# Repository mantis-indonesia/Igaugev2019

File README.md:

# Igaugev2019
Open source hardware water pressure sensor measurement system using Arduino Mega 2560

# Development
This system develop by Team MANTIS ID collaborate with USAID - IUWASH PLUS, PDAM Tirta Pakuan Kota Bogor, PDAM Tirta Patriot Kota Bekasi, and PDAM Tirta Asasta Kota Depok

# Folder
1. **Arduino Library** : All arduino external library used in this development
2. **Igauge_V2019** : Arduino Sketch used in this system
3. **Manual & Material** : All datasheet, and learning materials from components used in this system
4. **WEMOS_IGAUGE** : Arduino sketch for ESP Unit System
5. **nRFRangeTestRX** : Arduino sketch for NRF24L01 Experiment. This sketch used in server side
6. **nRFRangeTestTX** : Arduino sketch for NRF24L01 Experiment. This sketch used in transmitter side

# Developer
- Hollanda Arief Kusuma : github.com/hollandacocobear
- Rady P

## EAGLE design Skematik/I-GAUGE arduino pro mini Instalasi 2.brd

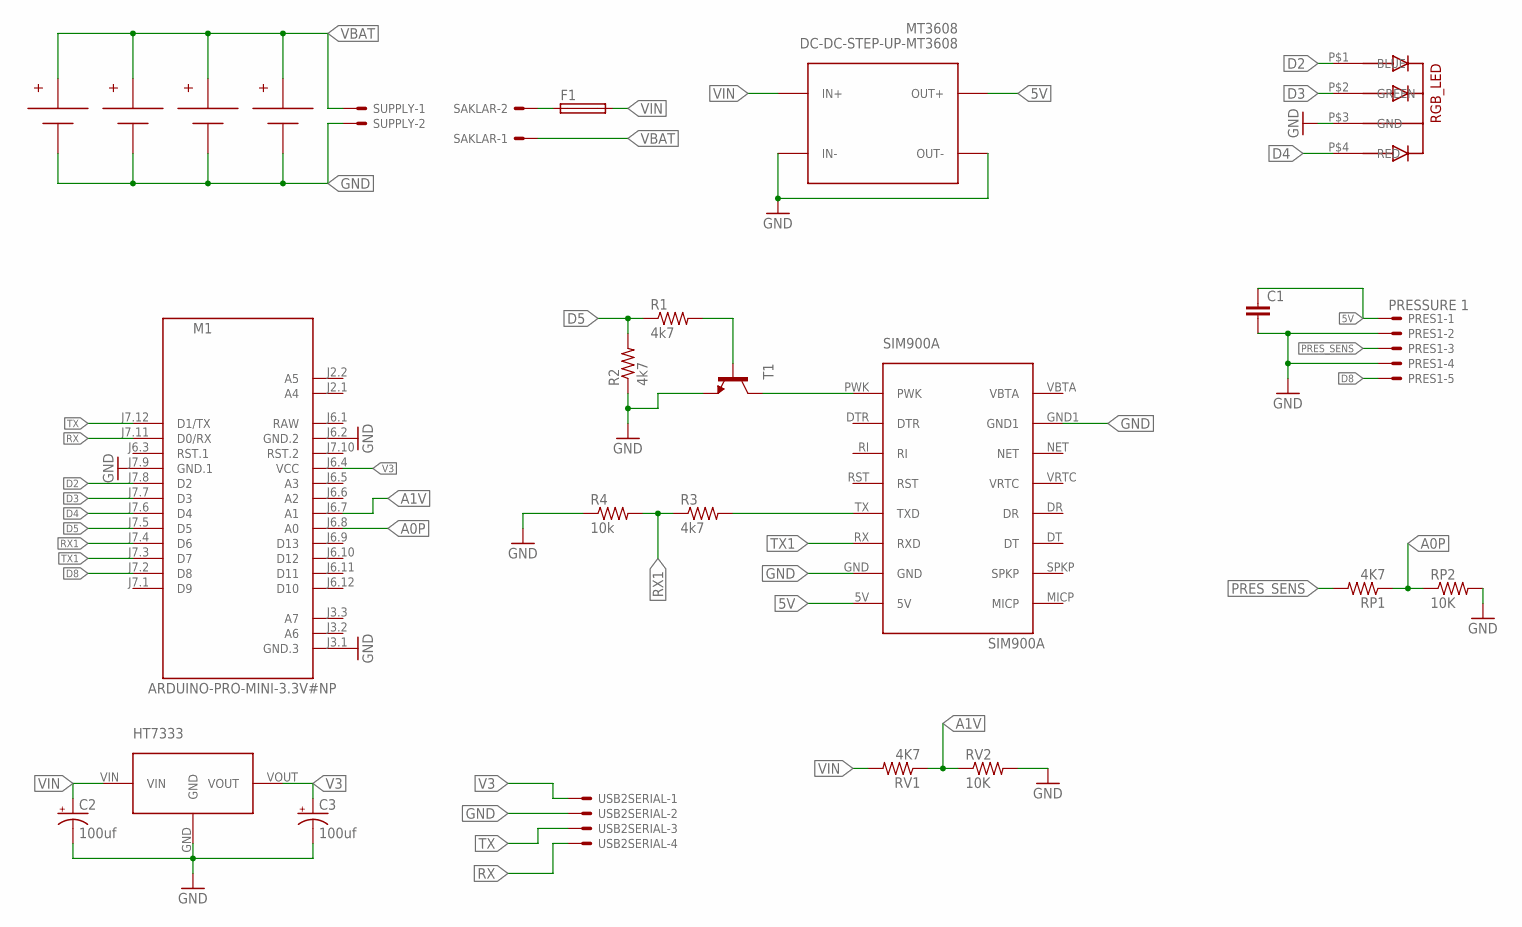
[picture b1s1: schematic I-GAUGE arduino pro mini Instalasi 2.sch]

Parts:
C1: C-EUC1206; C1206
C2, C3: 100uf; CT7343
F1: FUSESH22,5; SH22,5
HT7333: HT7333_SOT89; SOT89
M1: ARDUINO-PRO-MINI-3.3V#NP; ARDUINO-PRO-MINI#NP
MT3608: DC-DC-STEP-UP-MT3608
PRES1: PRESSURE 1; JST-XH-05-PACKAGE-ROUND-PAD
R1, R2: 4k7; R1206
R3: 4k7; 1206
R4: 10k; R1206
RGB_LED: 5MMRGBLED; LED5MMRGB
RP1: 4K7; M1206
RP2: 10K; M1206
RV1: 4K7; M1206
RV2: 10K; M1206
SAKLAR: JST-XH-02-PIN-ROUND-PAD; JST-XH-02-PACKAGE-ROUND-PAD
SUPPLY: JST-XH-02-PIN-ROUND-PAD; JST-XH-02-PACKAGE-ROUND-PAD
T1: -NPN-TO92; TO92
U$1, U$2, U$3, U$4: SMT18650; 18650SMT
U$6: SIM900A
USB2SERIAL: JST-XH-04-PIN-ROUND-PAD; JST-XH-04-PACKAGE-ROUND-PAD

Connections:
5V: C1.1, MT3608.OUT+, PRES1.1, U$6.5V
A0P: M1.J6.8 (A0), RP1.1, RP2.1
A1V: M1.J6.7 (A1), RV1.1, RV2.1
D2: M1.J7.8 (D2), RGB_LED.P$1 (BLUE)
D3: M1.J7.7 (D3), RGB_LED.P$2 (GREEN)
D4: M1.J7.6 (D4), RGB_LED.P$4 (RED)
D5: M1.J7.5 (D5), R1.1, R2.2
D8: M1.J7.2 (D8), PRES1.5
GND: C1.2, C2.-, C3.-, HT7333.GND, M1.J3.1 (GND.3), M1.J6.2 (GND.2), M1.J7.9 (GND.1), MT3608.IN-, MT3608.OUT-, PRES1.2, PRES1.4, R2.1, R4.1, RGB_LED.P$3 (GND), RP2.2, RV2.2, SUPPLY.2, T1.1 (E), U$1.BATTERY_NEGATIVE (-), U$2.BATTERY_NEGATIVE (-), U$3.BATTERY_NEGATIVE (-), U$4.BATTERY_NEGATIVE (-), U$6.GND, U$6.GND1, USB2SERIAL.2
unnamed: R1.2, T1.2 (B)
unnamed: R3.2, U$6.TX (TXD)
unnamed: T1.3 (C), U$6.PWK
PRES_SENS: PRES1.3, RP1.2
RAW: M1.J6.1 (RAW)
RX: M1.J7.11 (D0/RX), USB2SERIAL.4
RX1: M1.J7.4 (D6), R3.1, R4.2
TX: M1.J7.12 (D1/TX), USB2SERIAL.3
TX1: M1.J7.3 (D7), U$6.RX (RXD)
V3: C3.+, HT7333.VOUT, M1.J6.4 (VCC), USB2SERIAL.1
VBAT: SAKLAR.1, SUPPLY.1, U$1.BATTERY_POSITIVE (+), U$2.BATTERY_POSITIVE (+), U$3.BATTERY_POSITIVE (+), U$4.BATTERY_POSITIVE (+)
VCC: F1.1, SAKLAR.2
VIN: C2.+, F1.2, HT7333.VIN, MT3608.IN+, RV1.2

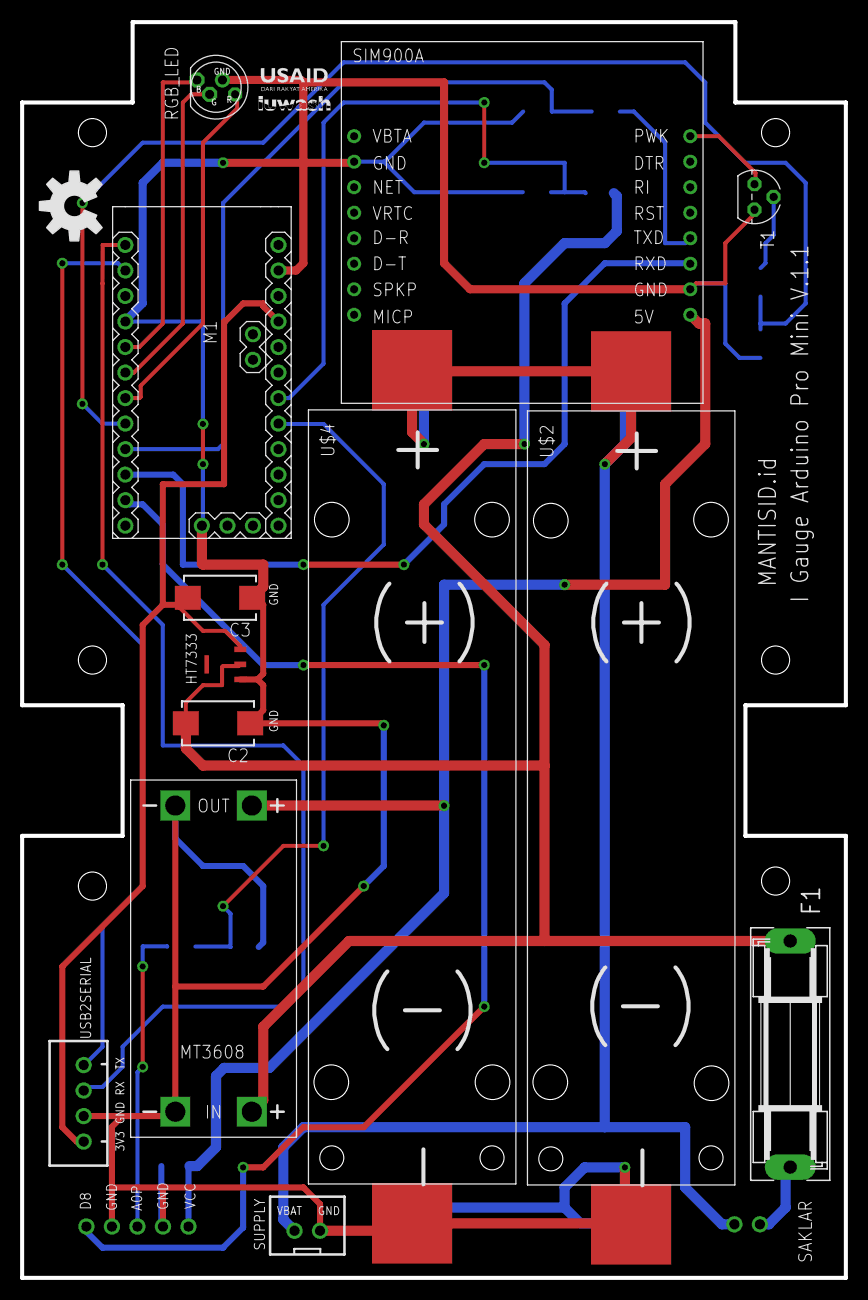
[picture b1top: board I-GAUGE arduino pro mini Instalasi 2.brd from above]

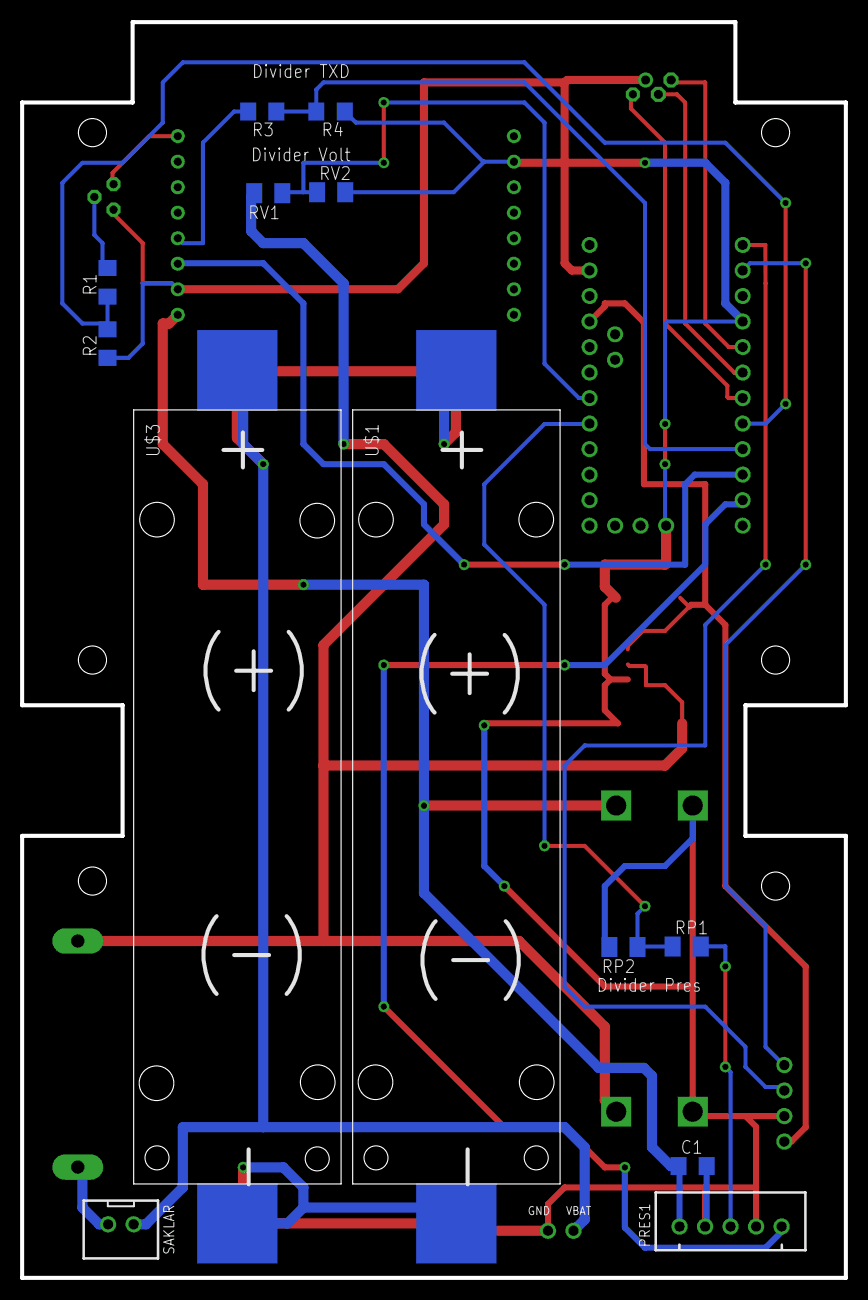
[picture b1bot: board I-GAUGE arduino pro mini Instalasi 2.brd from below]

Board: 2 copper layers, 82.0 x 125.0 mm, 27 parts (13 on the bottom side), 21 nets.

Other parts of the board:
U$7: OSHW-LOGO-L

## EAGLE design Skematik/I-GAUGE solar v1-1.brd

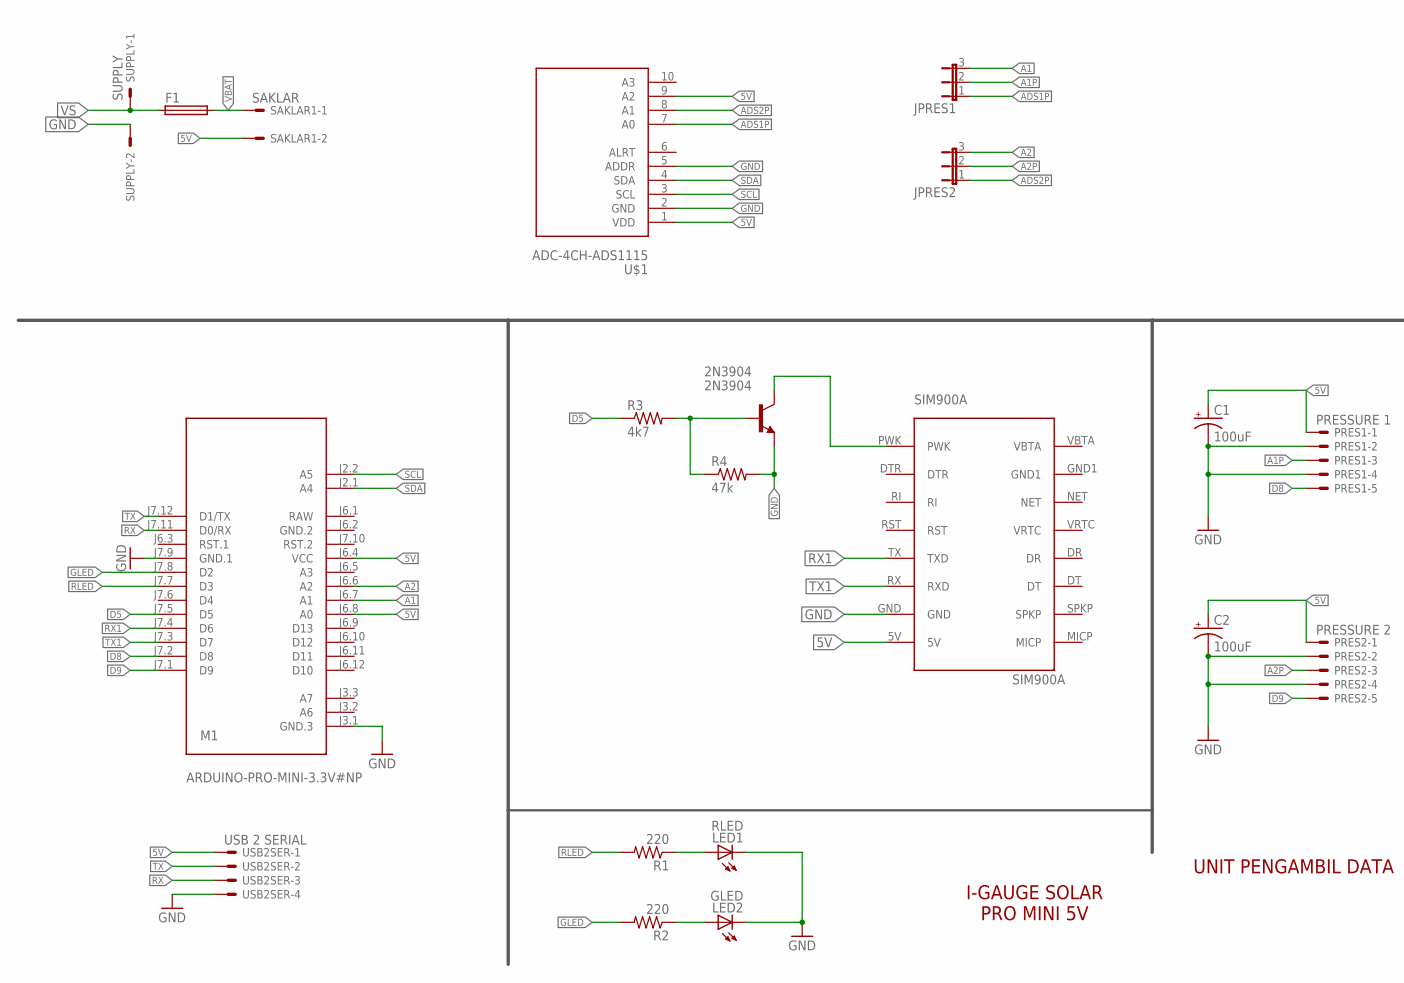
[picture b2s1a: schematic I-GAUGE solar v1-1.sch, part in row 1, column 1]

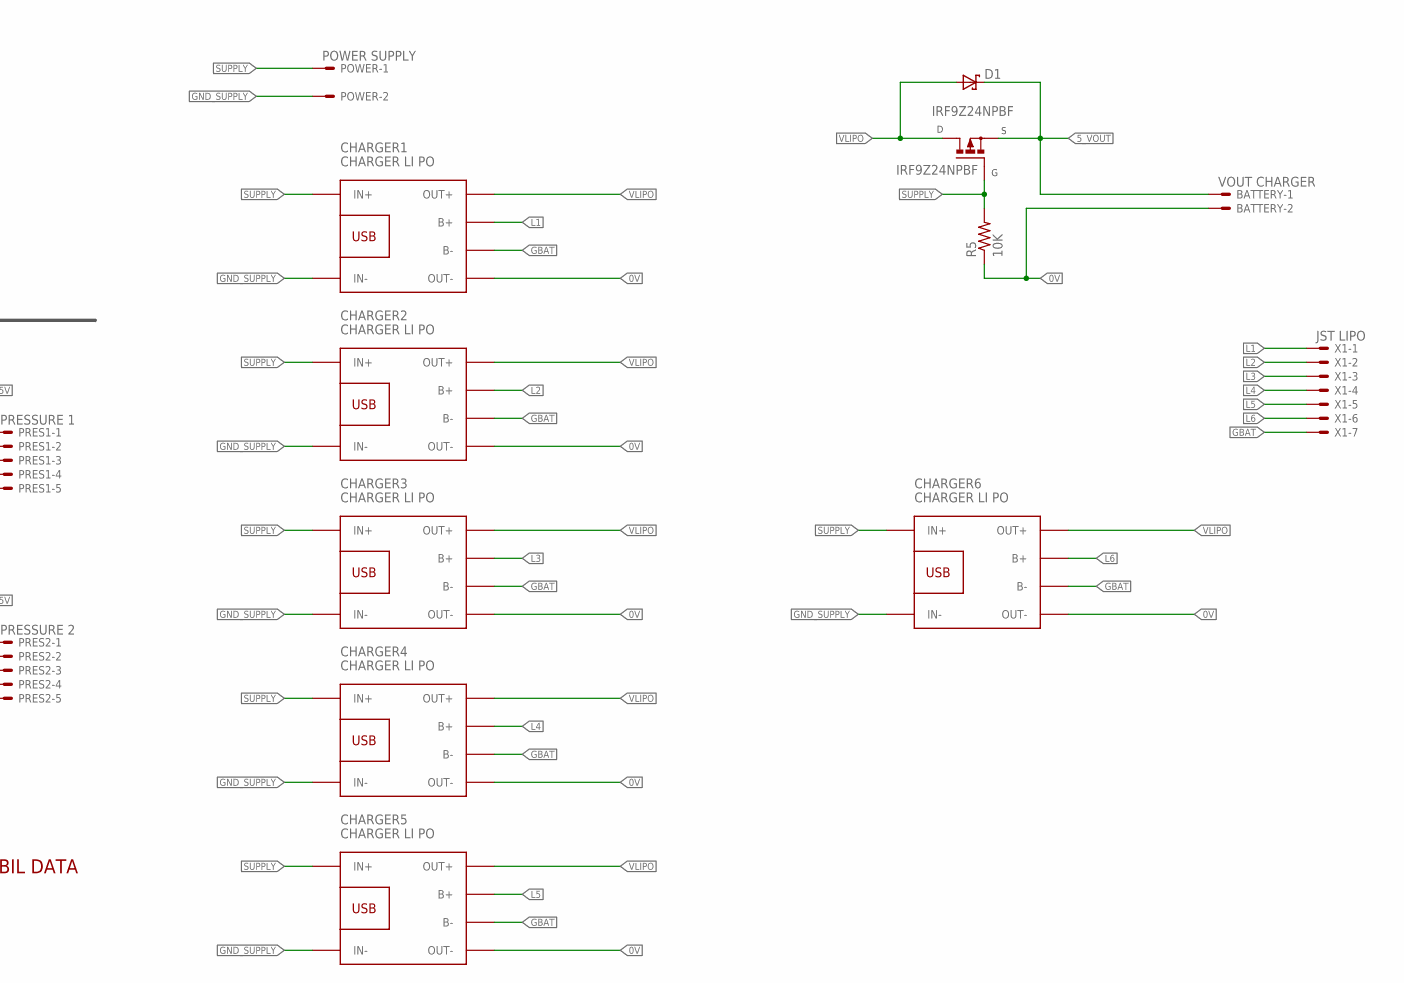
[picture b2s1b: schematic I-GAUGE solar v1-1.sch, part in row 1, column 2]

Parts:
2N3904: 2N3904; TO92
BATTERY: VOUT CHARGER; JST-XH-02-PACKAGE-ROUND-PAD
C1, C2: 100uF; EIA7343
CHARGER1, CHARGER2, CHARGER3, CHARGER4, CHARGER5, CHARGER6: CHARGER LI PO; BATTERY-CHARGER-LI-PROT
D1: DS_E2L; E2LINE
F1: FUSESH22,5; SH22,5
IRF9Z24NPBF: IRF9Z24NPBF; TO220BH
JPRES1, JPRES2: JP2E; JP2
LED1: RLED; LED5MM
LED2: GLED; LED5MM
M1: ARDUINO-PRO-MINI-3.3V#NP; ARDUINO-PRO-MINI#NP
POWER: POWER SUPPLY; JST-XH-02-PACKAGE-ROUND-PAD
PRES1: PRESSURE 1; JST-XH-05-PACKAGE-ROUND-PAD
PRES2: PRESSURE 2; JST-XH-05-PACKAGE-ROUND-PAD
R1, R2: 220; M1206
R3: 4k7; R0805
R4: 47k; R0805
R5: 10K; R0805
SAKLAR1: SAKLAR; JST-XH-02-PACKAGE-ROUND-PAD
SUPPLY: SUPPLY; JST-XH-02-PACKAGE-ROUND-PAD
U$1: ADC-4CH-ADS1115
U$5: SIM900A
USB2SER: USB 2 SERIAL; JST-XH-04-PACKAGE-ROUND-PAD
X1: JST LIPO; JST-XH-07-PACKAGE-ROUND-PAD

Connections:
0V: BATTERY.2, CHARGER1.OUT-, CHARGER2.OUT-, CHARGER3.OUT-, CHARGER4.OUT-, CHARGER5.OUT-, CHARGER6.OUT-, R5.1
5V: C1.A (+), C2.A (+), M1.J6.4 (VCC), M1.J6.8 (A0), PRES1.1, PRES2.1, SAKLAR1.2, U$1.1 (VDD), U$1.9 (A2), U$5.5V, USB2SER.1
5_VOUT: BATTERY.1, D1.1 (K), IRF9Z24NPBF.S
A1: JPRES1.3, M1.J6.7 (A1)
A1P: JPRES1.2, PRES1.3
A2: JPRES2.3, M1.J6.6 (A2)
A2P: JPRES2.2, PRES2.3
ADS1P: JPRES1.1, U$1.7 (A0)
ADS2P: JPRES2.1, U$1.8 (A1)
D5: M1.J7.5 (D5), R3.1
D8: M1.J7.2 (D8), PRES1.5
D9: M1.J7.1 (D9), PRES2.5
GBAT: CHARGER1.B-, CHARGER2.B-, CHARGER3.B-, CHARGER4.B-, CHARGER5.B-, CHARGER6.B-, X1.7
GLED: M1.J7.8 (D2), R2.2
GND: 2N3904.3 (E), C1.C (-), C2.C (-), LED1.K (C), LED2.K (C), M1.J3.1 (GND.3), M1.J7.9 (GND.1), PRES1.2, PRES1.4, PRES2.2, PRES2.4, R4.2, SUPPLY.2, U$1.2 (GND), U$1.5 (ADDR), U$5.GND, USB2SER.4
GND.2: M1.J6.2 (GND.2)
GND_SUPPLY: CHARGER1.IN-, CHARGER2.IN-, CHARGER3.IN-, CHARGER4.IN-, CHARGER5.IN-, CHARGER6.IN-, POWER.2
L1: CHARGER1.B+, X1.1
L2: CHARGER2.B+, X1.2
L3: CHARGER3.B+, X1.3
L4: CHARGER4.B+, X1.4
L5: CHARGER5.B+, X1.5
L6: CHARGER6.B+, X1.6
unnamed: 2N3904.1 (C), U$5.PWK
unnamed: LED1.A, R1.1
unnamed: LED2.A, R2.1
unnamed: 2N3904.2 (B), R3.2, R4.1
RAW: M1.J6.1 (RAW)
RLED: M1.J7.7 (D3), R1.2
RX: M1.J7.11 (D0/RX), USB2SER.3
RX1: M1.J7.4 (D6), U$5.TX (TXD)
SCL: M1.J2.2 (A5), U$1.3 (SCL)
SDA: M1.J2.1 (A4), U$1.4 (SDA)
SUPPLY: CHARGER1.IN+, CHARGER2.IN+, CHARGER3.IN+, CHARGER4.IN+, CHARGER5.IN+, CHARGER6.IN+, IRF9Z24NPBF.G, POWER.1, R5.2
TX: M1.J7.12 (D1/TX), USB2SER.2
TX1: M1.J7.3 (D7), U$5.RX (RXD)
VBAT: F1.2, SAKLAR1.1
VLIPO: CHARGER1.OUT+, CHARGER2.OUT+, CHARGER3.OUT+, CHARGER4.OUT+, CHARGER5.OUT+, CHARGER6.OUT+, D1.2 (A), IRF9Z24NPBF.D
VS: F1.1, SUPPLY.1

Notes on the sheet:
I-GAUGE SOLAR PRO MINI 5V
UNIT PENGAMBIL DATA

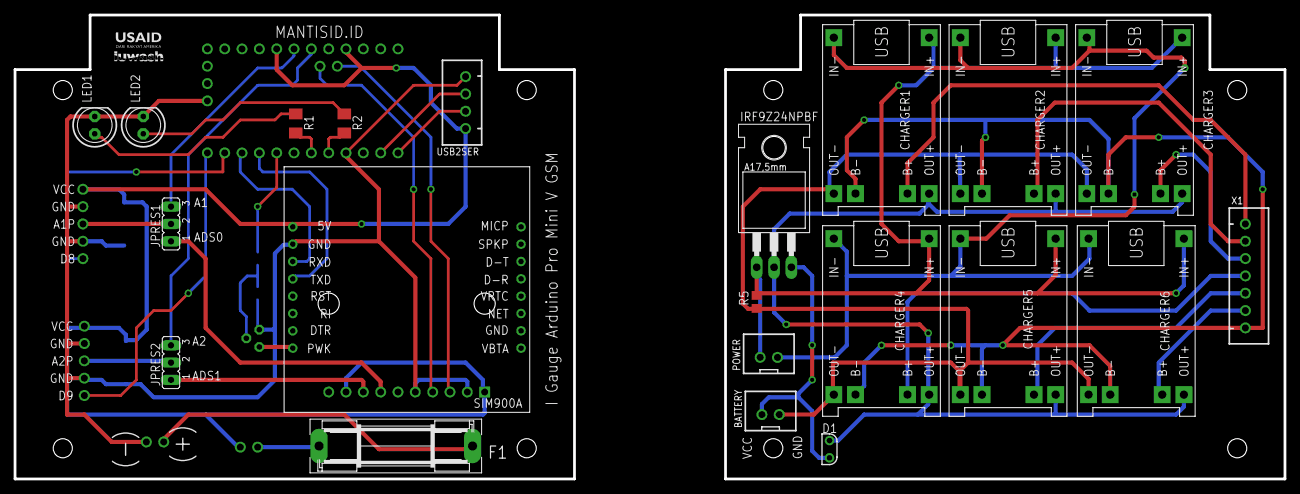
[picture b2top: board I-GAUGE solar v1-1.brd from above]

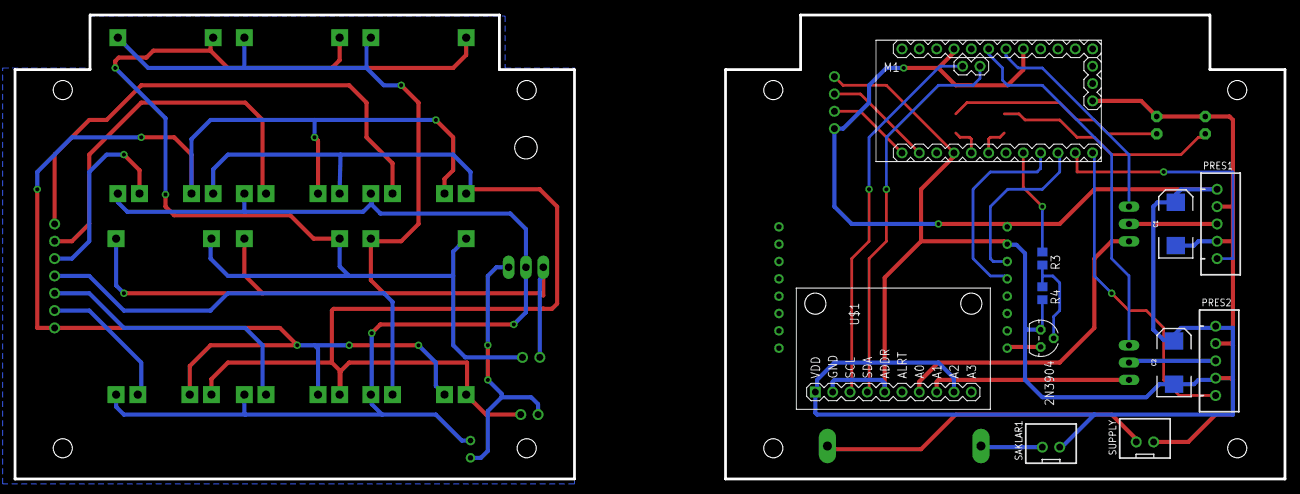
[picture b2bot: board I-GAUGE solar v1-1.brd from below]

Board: 2 copper layers, 186.1 x 68.0 mm, 32 parts (11 on the bottom side), 37 nets.

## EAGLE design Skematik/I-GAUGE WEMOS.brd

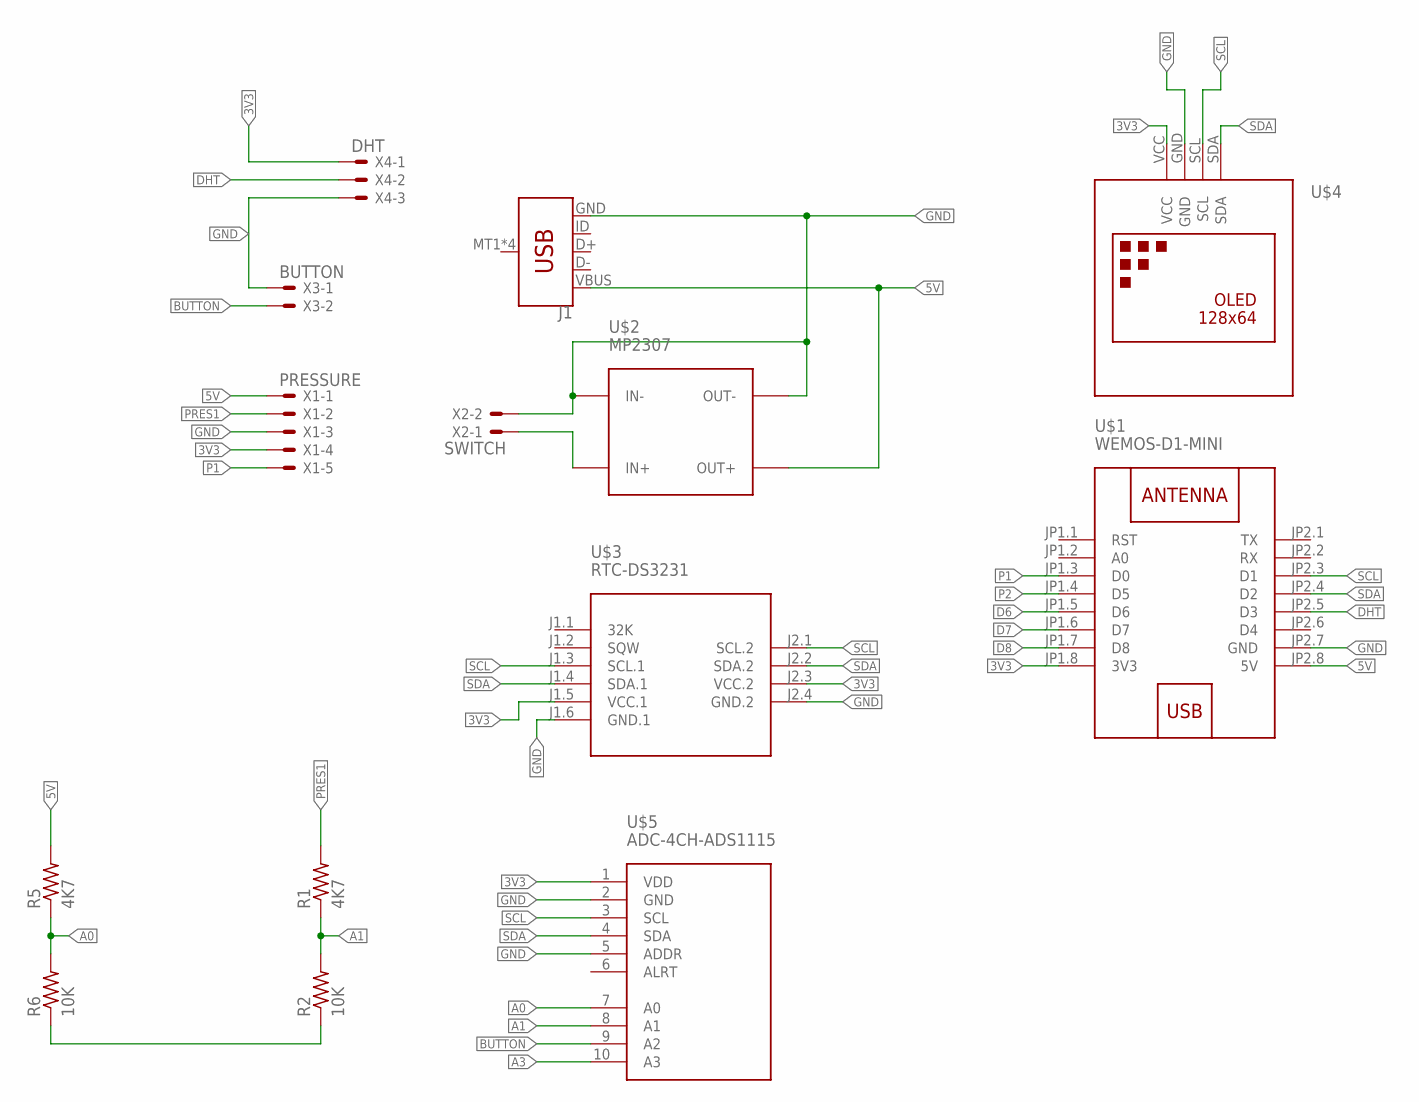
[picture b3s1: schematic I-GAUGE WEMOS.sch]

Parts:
J1: USB_MICRO-B_SMT; USB-MICROB
R1, R5: 4K7; R1210
R2, R6: 10K; R1210
U$1: WEMOS-D1-MINI
U$2: MP2307; DC-DC-STEP-DOWN-MP2307
U$3: RTC-DS3231; RTC-DS3231-AT24C32
U$4: DISPLAY-OLED-128X64-I2C
U$5: ADC-4CH-ADS1115
X1: PRESSURE; JST-XH-05-PACKAGE-LONG-PAD
X2: SWITCH; JST-XH-02-PACKAGE-LONG-PAD
X3: BUTTON; JST-XH-02-PACKAGE-LONG-PAD
X4: DHT; JST-XH-03-PACKAGE-LONG-PAD

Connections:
3V3: U$1.JP1.8 (3V3), U$3.J1.5 (VCC.1), U$3.J2.3 (VCC.2), U$4.VCC, U$5.1 (VDD), X1.4, X4.1
5V: J1.VBUS, R5.2, U$1.JP2.8 (5V), U$2.OUT+, X1.1
A0: R5.1, R6.2, U$5.7 (A0)
A1: R1.1, R2.2, U$5.8 (A1)
A3: U$5.10 (A3)
BUTTON: U$5.9 (A2), X3.2
D6: U$1.JP1.5 (D6)
D7: U$1.JP1.6 (D7)
D8: U$1.JP1.7 (D8)
DHT: U$1.JP2.5 (D3), X4.2
GND: J1.GND, R2.1, R6.1, U$1.JP2.7 (GND), U$2.IN-, U$2.OUT-, U$3.J1.6 (GND.1), U$3.J2.4 (GND.2), U$4.GND, U$5.2 (GND), U$5.5 (ADDR), X1.3, X2.2, X3.1, X4.3
unnamed: U$2.IN+, X2.1
P1: U$1.JP1.3 (D0), X1.5
P2: U$1.JP1.4 (D5)
PRES1: R1.2, X1.2
SCL: U$1.JP2.3 (D1), U$3.J1.3 (SCL.1), U$3.J2.1 (SCL.2), U$4.SCL, U$5.3 (SCL)
SDA: U$1.JP2.4 (D2), U$3.J1.4 (SDA.1), U$3.J2.2 (SDA.2), U$4.SDA, U$5.4 (SDA)

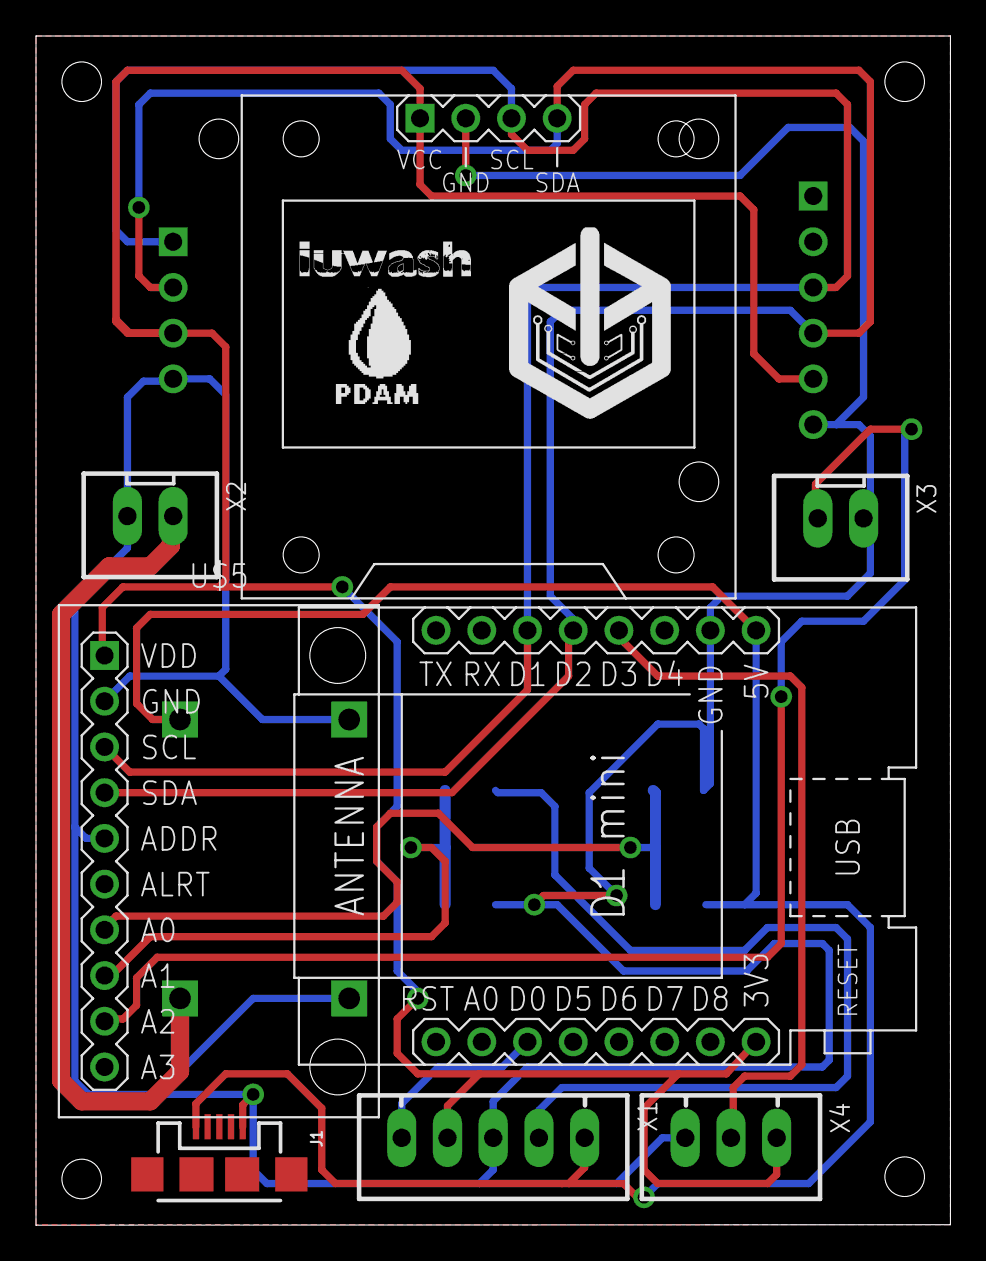
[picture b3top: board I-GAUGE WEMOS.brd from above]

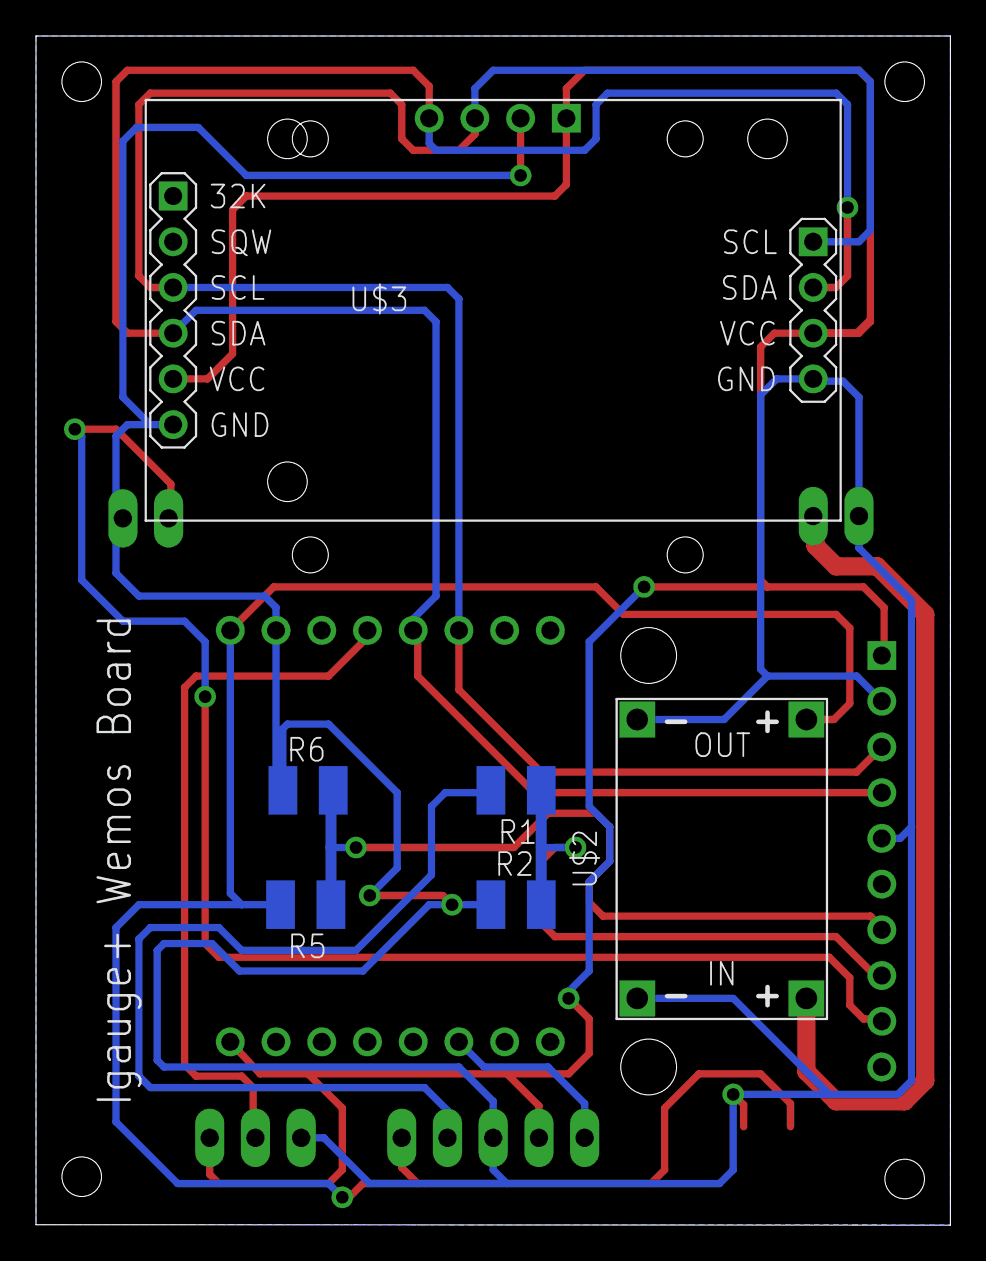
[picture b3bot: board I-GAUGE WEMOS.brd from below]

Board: 2 copper layers, 50.8 x 66.1 mm, 14 parts (6 on the bottom side), 12 nets.

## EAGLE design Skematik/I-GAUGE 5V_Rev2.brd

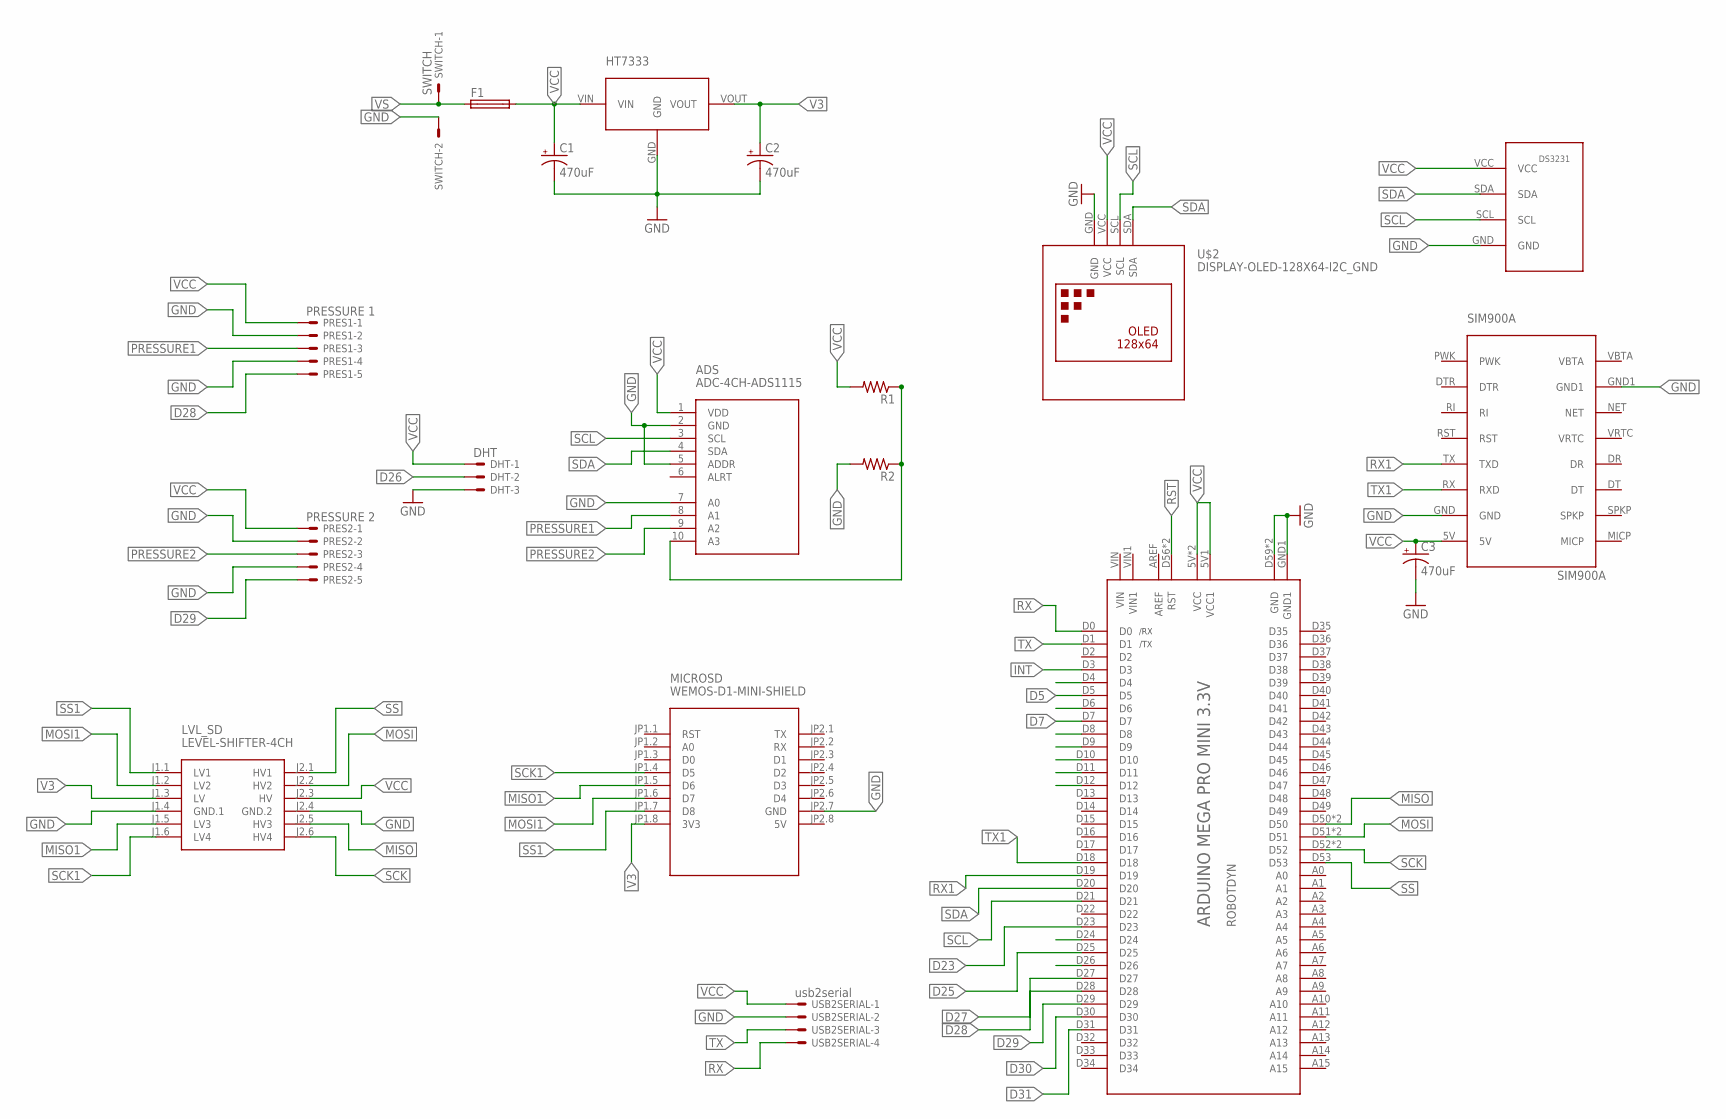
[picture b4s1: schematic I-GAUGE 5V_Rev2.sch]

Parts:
ADS: ADC-4CH-ADS1115
C1, C2, C3: 470uF; PANASONIC_G
DHT: DHT; JST-XH-03-PACKAGE-ROUND-PAD
F1: FUSESH22,5; SH22,5
HT7333: HT7333; SOT89
LVL_SD: LEVEL-SHIFTER-4CH
MICROSD: WEMOS-D1-MINI-SHIELD
PRES1: PRESSURE 1; JST-XH-05-PACKAGE-ROUND-PAD
PRES2: PRESSURE 2; JST-XH-05-PACKAGE-ROUND-PAD
R1, R2: R-US_M1206; M1206
SWITCH: SWITCH; JST-XH-02-PACKAGE-ROUND-PAD
U$1: MEGA-PRO-MINI
U$2: DISPLAY-OLED-128X64-I2C_GND
U$5: DS3231_RASP
U$6: SIM900A
USB2SERIAL: usb2serial; JST-XH-04-PACKAGE-ROUND-PAD

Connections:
5V: MICROSD.JP2.8 (5V)
D4: U$1.D4
D5: U$1.D5
D6: U$1.D6
D7: U$1.D7
D8: U$1.D8
D9: U$1.D9
D10: U$1.D10
D11: U$1.D11
D12: U$1.D12
D23: U$1.D23
D24: U$1.D24
D25: U$1.D25
D26: DHT.2, U$1.D26
D27: U$1.D27
D28: PRES1.5, U$1.D28
D29: PRES2.5, U$1.D29
D30: U$1.D30
D31: U$1.D31
GND: ADS.2 (GND), ADS.5 (ADDR), ADS.7 (A0), C1.-, C2.-, C3.-, DHT.3, HT7333.GND, LVL_SD.J1.4 (GND.1), LVL_SD.J2.4 (GND.2), MICROSD.JP2.7 (GND), PRES1.2, PRES1.4, PRES2.2, PRES2.4, R2.2, SWITCH.2, U$1.D59 (GND), U$1.GND, U$1.GND1, U$2.GND, U$5.GND, U$6.GND, U$6.GND1, USB2SERIAL.2
INT: U$1.D3
MISO: LVL_SD.J2.5 (HV3), U$1.D50, U$1.D54 (D50)
MISO1: LVL_SD.J1.5 (LV3), MICROSD.JP1.5 (D6)
MOSI: LVL_SD.J2.2 (HV2), U$1.D51, U$1.D58 (D51)
MOSI1: LVL_SD.J1.2 (LV2), MICROSD.JP1.6 (D7)
PRESSURE1: ADS.8 (A1), PRES1.3
PRESSURE2: ADS.9 (A2), PRES2.3
RST: U$1.D56 (RST), U$1.RST
RX: U$1.D0, USB2SERIAL.4
RX1: U$1.D19, U$6.TX (TXD)
SCK: LVL_SD.J2.6 (HV4), U$1.D52, U$1.D55 (D52)
SCK1: LVL_SD.J1.6 (LV4), MICROSD.JP1.4 (D5)
SCL: ADS.3 (SCL), U$1.D21, U$2.SCL, U$5.SCL
SDA: ADS.4 (SDA), U$1.D20, U$2.SDA, U$5.SDA
SS: LVL_SD.J2.1 (HV1), U$1.D53
SS1: LVL_SD.J1.1 (LV1), MICROSD.JP1.7 (D8)
TX: U$1.D1, USB2SERIAL.3
TX1: U$1.D18, U$6.RX (RXD)
V3: C2.+, HT7333.VOUT, LVL_SD.J1.3 (LV), MICROSD.JP1.8 (3V3)
VCC: ADS.1 (VDD), ADS.10 (A3), C1.+, C3.+, DHT.1, F1.2, HT7333.VIN, LVL_SD.J2.3 (HV), PRES1.1, PRES2.1, R1.1, R1.2, R2.1, U$1.5V (VCC), U$1.5V1 (VCC1), U$1.D57 (VCC), U$2.VCC, U$5.VCC, U$6.5V, USB2SERIAL.1
VS: F1.1, SWITCH.1

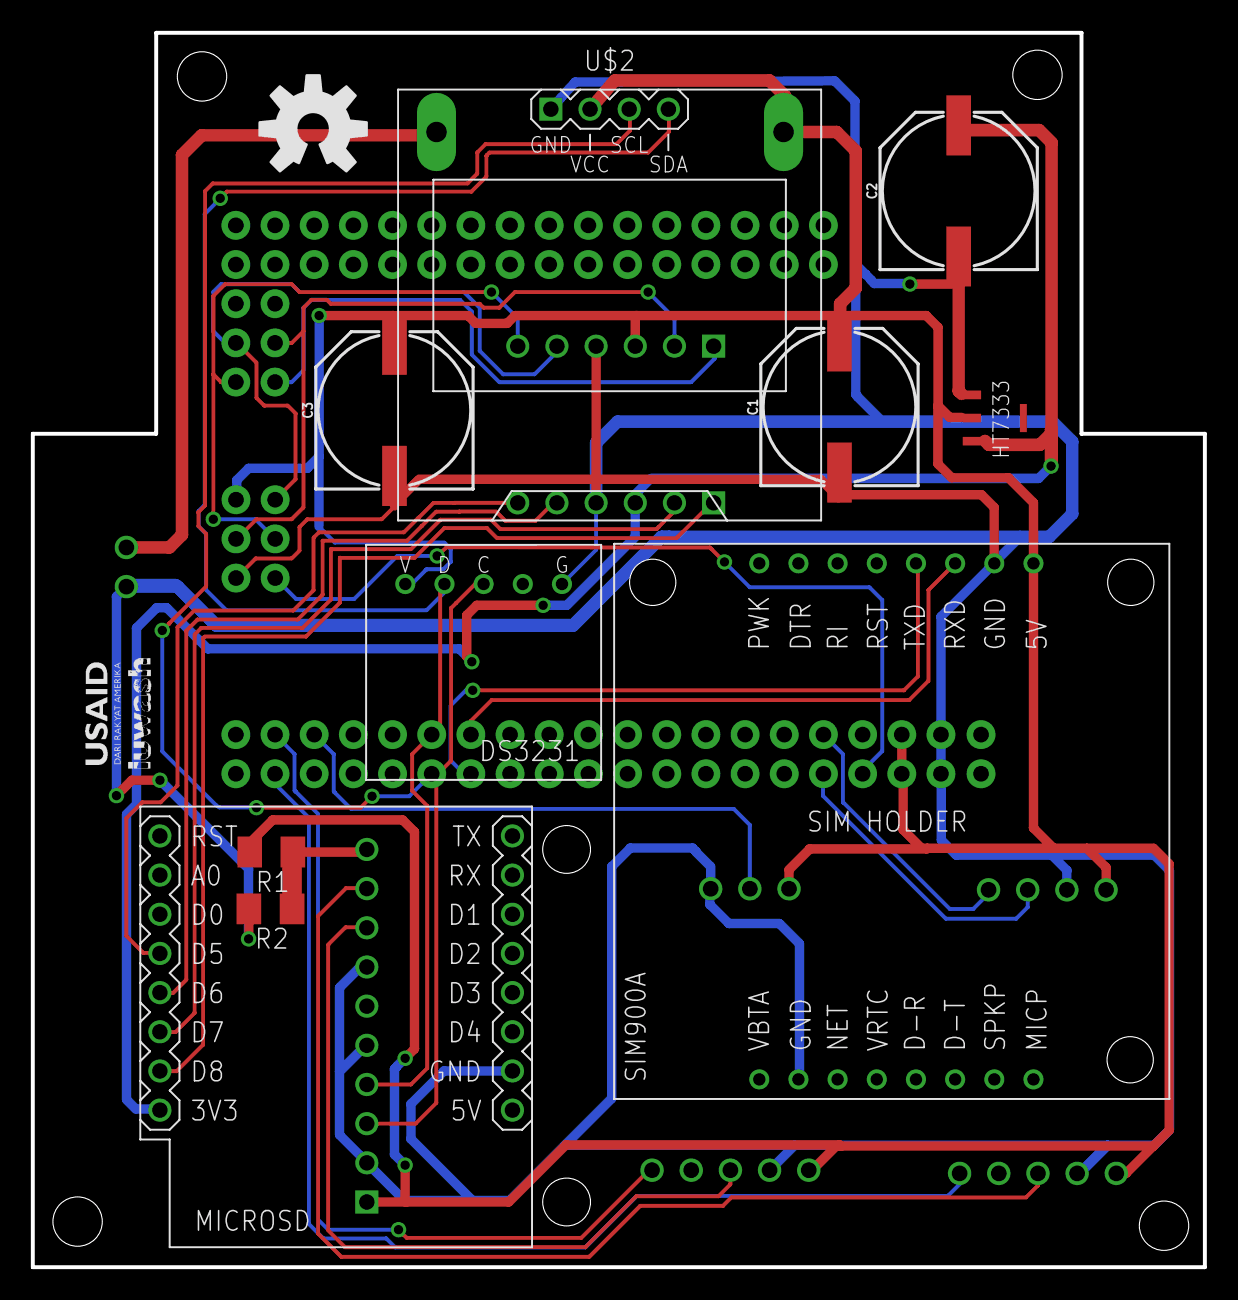
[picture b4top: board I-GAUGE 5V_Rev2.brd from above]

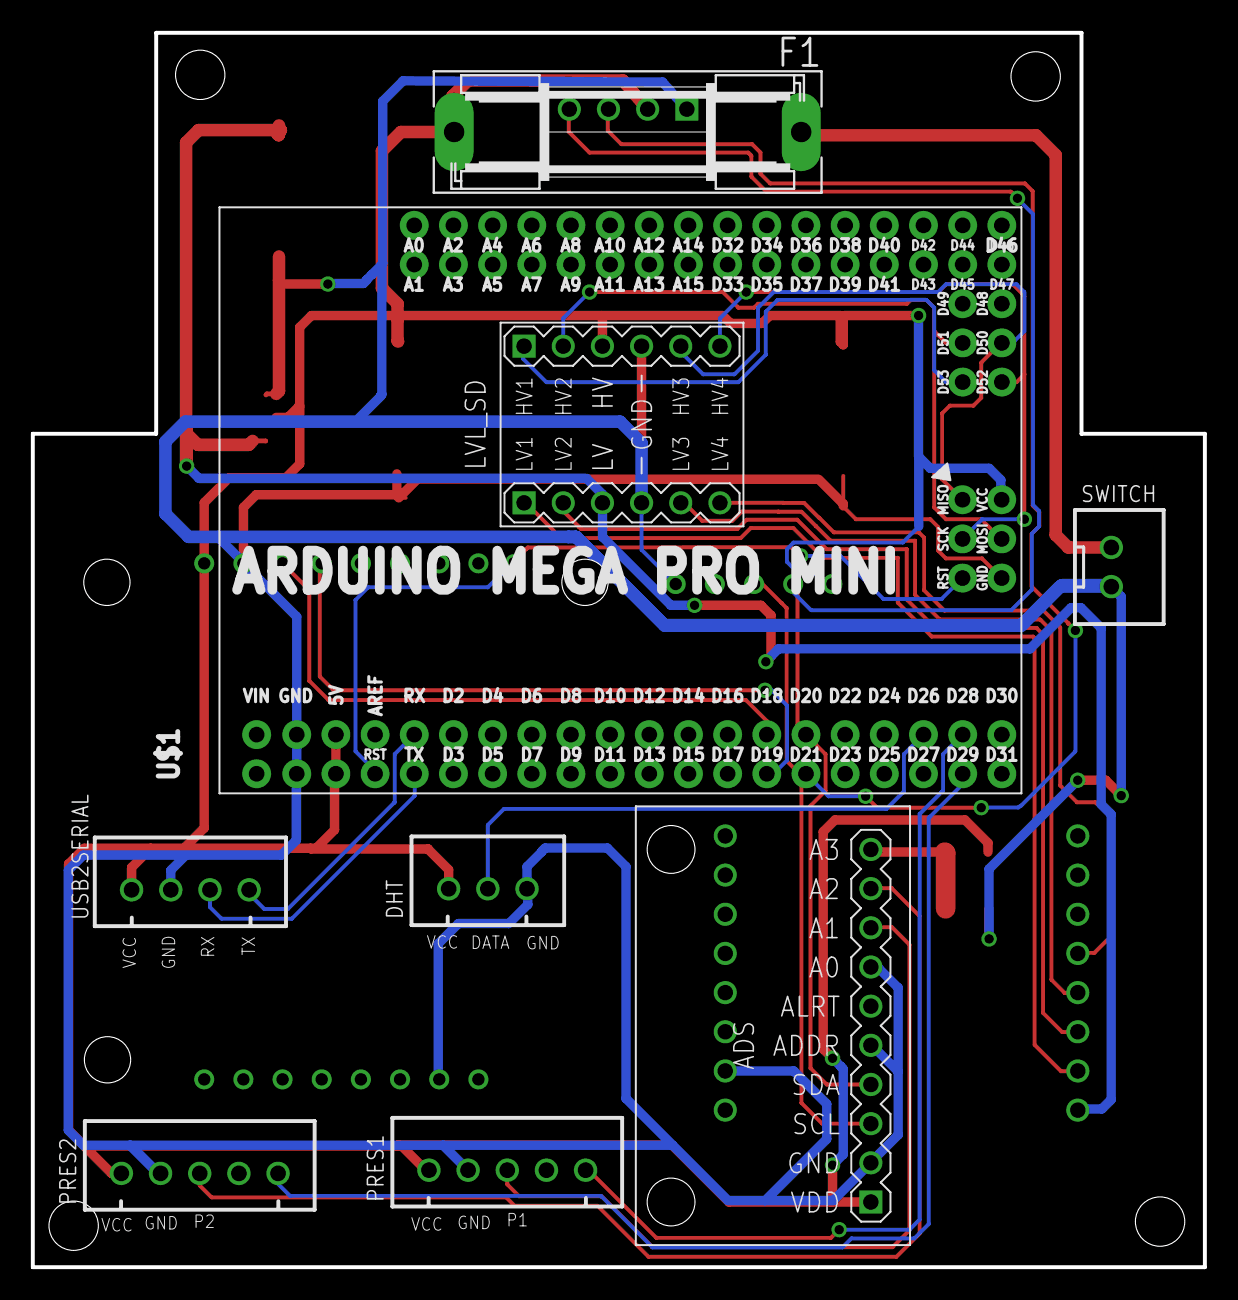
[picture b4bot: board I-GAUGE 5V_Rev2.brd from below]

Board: 2 copper layers, 76.0 x 80.0 mm, 20 parts (9 on the bottom side), 24 nets.

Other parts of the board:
U$4: OSHW-LOGO-L

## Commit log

2019-07-10 Add files via upload
    sktech igauge promini untuk instalasi 2
2020-02-16 Add files via upload
    MANUAL ASSEMBLY DEVICE
2020-02-17 Create MANUAL BOOK
    MANUAL BOOK FOR I-GAUGE LOGGER 2019
2020-02-17 Add files via upload
    FIRMWARE FOR SENDING TO THINGSPEAK

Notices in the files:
parts and their libraries:
diy-modules: Released under the Creative Commons Attribution 4.0 International License: http://creativecommons.org/licenses/by/4.0
SparkFun-Capacitors: Licensing: Creative Commons ShareAlike 4.0 International - https://creativecommons.org/licenses/by-sa/4.0
